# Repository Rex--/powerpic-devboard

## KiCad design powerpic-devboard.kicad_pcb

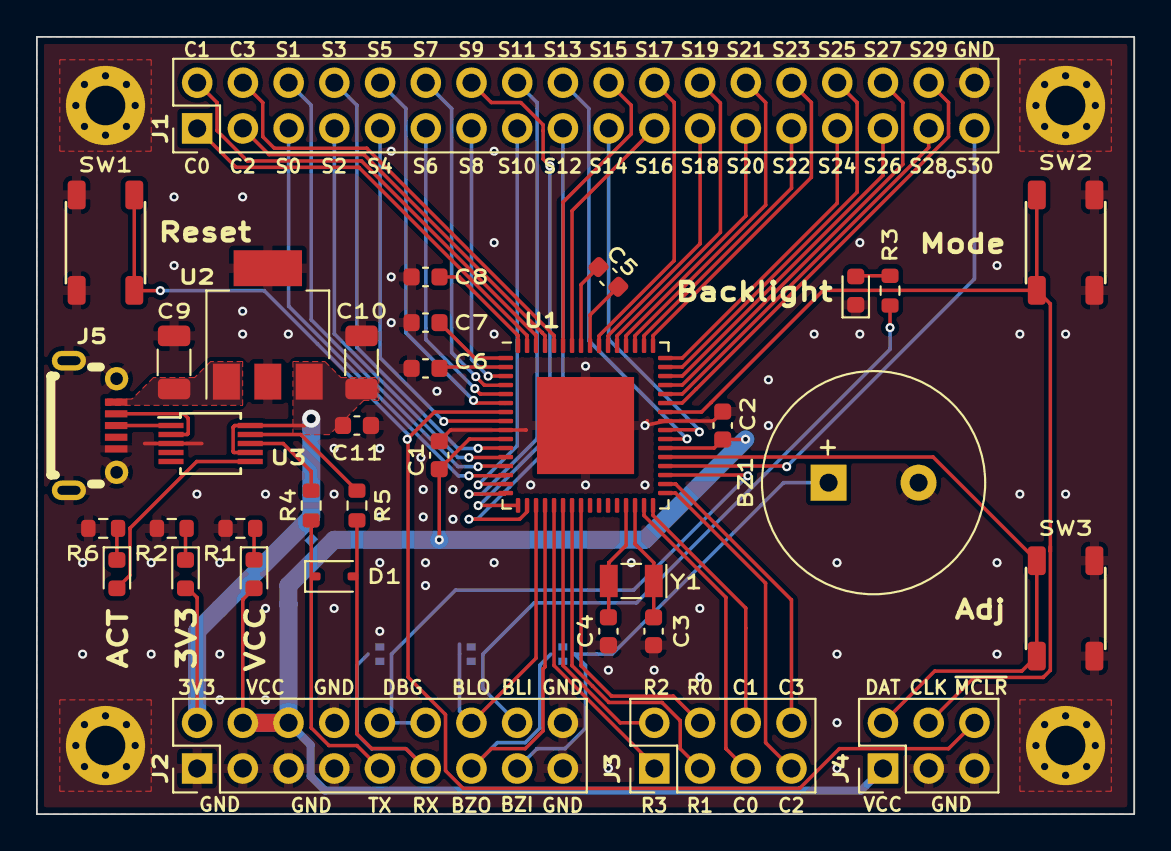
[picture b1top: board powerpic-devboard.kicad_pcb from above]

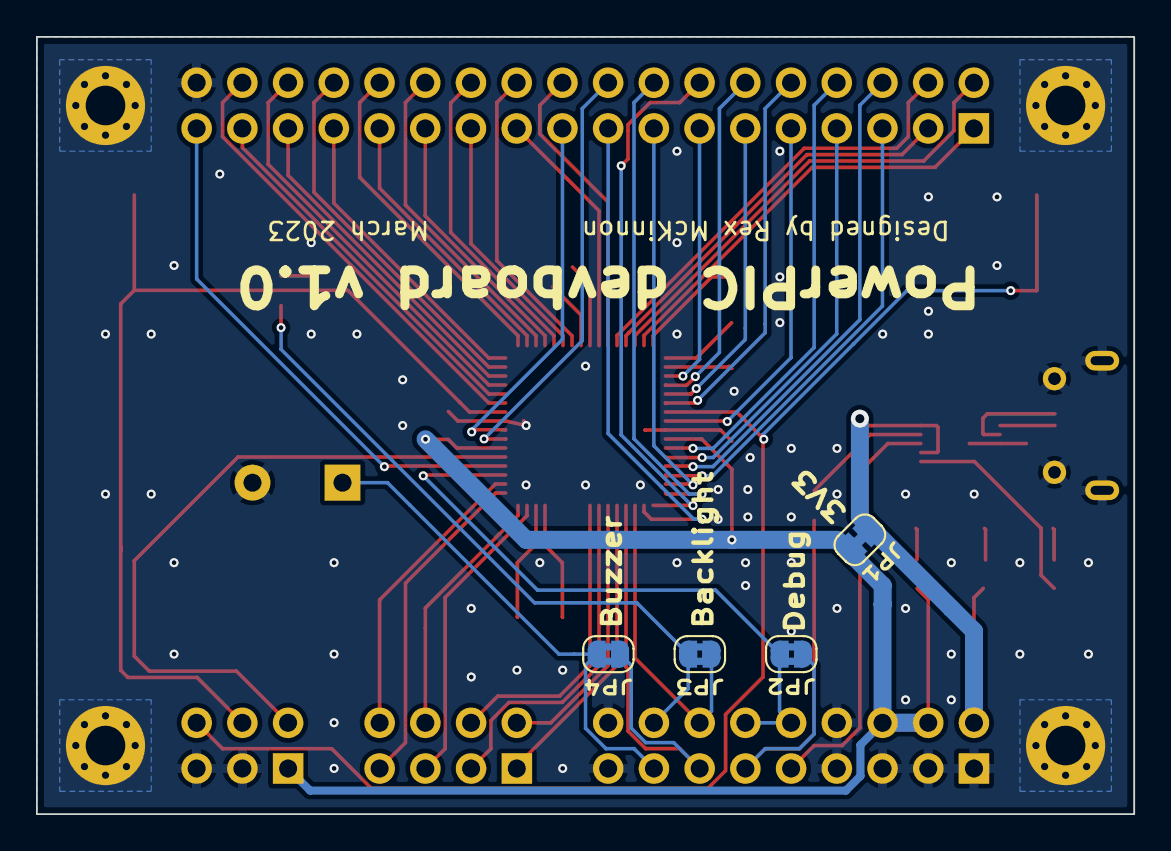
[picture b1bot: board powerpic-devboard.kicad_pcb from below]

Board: 2 copper layers, 61.0 x 43.2 mm, 43 parts (4 on the bottom side), 73 nets.

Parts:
BZ1: Buzzer; Buzzer_12.2x6.5RM5
C1, C2, C11: 0.1µF; C_0603_1608Metric
C3, C4: TBD; C_0603_1608Metric
C5: 1μF; C_0603_1608Metric
C6, C7, C8: 0.27μF; C_0603_1608Metric
C9, C10: 4.7µF; C_1206_3216Metric
D1: D; D_SOD-323
H1, H2, H3, H4: MountingHole_Pad; MountingHole_2.2mm_M2_Pad_Via
J1: Display; PinHeader_2x18_P2.54mm_Vertical
J2: Misc I/O; PinHeader_2x09_P2.54mm_Vertical
J3: Keypad; PinHeader_2x04_P2.54mm_Vertical
J4: ICSP; PinHeader_2x03_P2.54mm_Vertical
J5: Micro USB; USB_Micro-B_Receptacle_AdamTech_MCR-B-S-RA-SMT-CS5A-NF-TR
JP1: 3V3_en; SolderJumper-2_P1.3mm_Bridged_RoundedPad1.0x1.5mm
JP2: Debug_en; SolderJumper-2_P1.3mm_Bridged2Bar_RoundedPad1.0x1.5mm
JP3: Backlight_en; SolderJumper-2_P1.3mm_Bridged2Bar_RoundedPad1.0x1.5mm
JP4: Buzzer_en; SolderJumper-2_P1.3mm_Bridged2Bar_RoundedPad1.0x1.5mm
LED1: VCC; LED_0603_1608Metric
LED2: 3V3; LED_0603_1608Metric
LED3: Backlight; LED_0603_1608Metric
LED4: ACT; LED_0603_1608Metric
R1, R2, R4, R5, R6: R; R_0603_1608Metric
R3: TBD; R_0603_1608Metric
SW1: Reset; Button_Push_SPST_C&K_PTS647Sx38SMTR2LFS
SW2: Mode; Button_Push_SPST_C&K_PTS647Sx38SMTR2LFS
SW3: Adj; Button_Push_SPST_C&K_PTS647Sx38SMTR2LFS
U1: PIC16LF19197-xMR; QFN-64-1EP_9x9mm_P0.5mm_EP5.4x5.4mm
U2: AP2114; SOT-223-3_TabPin2
U3: CH340E; MSOP-10_3x3mm_P0.5mm
Y1: 32.768kHz; Crystal_SMD_MicroCrystal_CC7V-T1A-2Pin_3.2x1.5mm

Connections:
+3V3: C10.1, C11.2, J2.2, JP1.1 (A), LED2.2 (A), U2.3 (VO), U3.7 (VCC), U3.10 (V3)
/BACKLIGHT: J2.14, JP3.1 (A), U1.19 (COM7/SEG15/RG7)
/BACKLIGHT_LED: J2.16, JP3.2 (B), R3.1
/BUZZER: J2.13, JP4.1 (A), U1.20 (COM6/RG6)
/BUZZER_ONB: BZ1.1 (-), J2.15, JP4.2 (B)
/COL0: J3.5, U1.31 (RC6/SEG27)
/COL1: J3.6, U1.32 (RC7/SEG28)
/COL2: J3.7, U1.33 (RC2/SEG13)
/COL3: J3.8, U1.34 (RC3/SEG17)
/COM0: J1.1, U1.63 (COM0/RE3)
/COM1: J1.2, U1.62 (COM1/RE4)
/COM2: J1.3, U1.61 (COM2/RE5)
/COM3: J1.4, U1.60 (COM3/RE6)
/DEBUG: J2.10, J2.12, JP2.2 (B), U1.35 (RC4/SEG16)
/ICSP_CLK: J4.4, SW2.2, U1.42 (RB6/SEG38/ICSPCLK)
/ICSP_DAT: J4.2, SW3.1, U1.37 (RB7/SEG39/ICSPDAT)
/ROW0: J3.4, U1.24 (RA0/SEG33)
/ROW1: J3.3, U1.23 (RA1/SEG18)
/ROW2: J3.2, U1.22 (RA2/SEG34)
/ROW3: J3.1, U1.21 (RA3/SEG35)
/SEG0: J1.5, U1.14 (SEG22/RF4)
/SEG1: J1.6, U1.13 (SEG23/RF5)
/SEG2: J1.7, U1.12 (SEG24/RF6)
/SEG3: J1.8, U1.11 (SEG25/RF7)
/SEG4: J1.9, U1.8 (SEG26/RG4)
/SEG5: J1.10, U1.6 (SEG45/RG3)
/SEG6: J1.11, U1.5 (SEG44/RG2)
/SEG7: J1.12, U1.4 (SEG43/RG1)
/SEG8: J1.13, U1.3 (SEG42/RG0)
/SEG9: J1.14, U1.17 (SEG19/RF1)
/SEG10: J1.15, U1.15 (SEG21/RF3)
/SEG11: J1.16, U1.16 (SEG20/RF2)
/SEG12: J1.17, U1.18 (SEG41/RF0)
/SEG13: J1.18, U1.39 (RA7/SEG37)
/SEG14: J1.19, U1.40 (RA6/SEG36)
/SEG15: J1.20, U1.59 (SEG31/RE7)
/SEG16: J1.21, U1.58 (RD0/SEG0)
/SEG17: J1.22, U1.55 (RD1/SEG1)
/SEG18: J1.23, U1.54 (RD2/SEG2)
/SEG19: J1.24, U1.53 (RD3/SEG3)
/SEG20: J1.25, U1.52 (RD4/SEG4)
/SEG21: J1.26, U1.51 (RD5/SEG5)
/SEG22: J1.27, U1.50 (RD6/SEG6)
/SEG23: J1.28, U1.49 (RD7/SEG7)
/SEG24: J1.29, U1.48 (RB0/SEG30)
/SEG25: J1.30, U1.47 (RB1/SEG8)
/SEG26: J1.31, U1.46 (RB2/SEG9)
/SEG27: J1.32, U1.45 (RB3/SEG10)
/SEG28: J1.33, U1.44 (RB4/SEG11)
/SEG29: J1.34, U1.43 (RB5/SEG29)
/SEG30: J1.35, U1.36 (RC5/SEG12)
/UART_RX: D1.2 (A), J2.11, JP2.1 (A), R5.2
/UART_TX: D1.1 (K), J2.9, R4.2
/~MCLR: J4.6, SW1.2, U1.7 (VPP/~MCLR/RG5)
GND: BZ1.2 (+), C1.2, C2.2, C3.2, C4.2, C6.2, C7.2, C8.2, C9.2, C10.2, C11.1, H1.1, H2.1, H3.1, H4.1, J1.36, J2.1, J2.3, J2.5, J2.7, J2.8, J2.17, J2.18, J4.3, J4.5, J5.5 (GND), J5.6 (Shield), LED3.1 (K), R1.2, R2.2, R6.2, SW1.1, SW2.1, SW3.2, U1.9 (VSS), U1.41 (VSS), U1.65 (VSS), U2.2 (GND), U3.3 (GND)
unnamed: J5.3 (D+), U3.1 (UD+)
unnamed: J5.2 (D-), U3.2 (UD-)
unnamed: LED1.1 (K), R1.1
unnamed: LED2.1 (K), R2.1
unnamed: LED3.2 (A), R3.2
unnamed: LED4.2 (A), U3.6 (TNOW)
unnamed: LED4.1 (K), R6.1
unnamed: C5.2, U1.57 (CFLY1/SEG32/RH2)
unnamed: C5.1, U1.56 (CFLY2/SEG40/RH3)
unnamed: C3.1, U1.30 (RC0), Y1.1
unnamed: C4.1, U1.29 (RC1), Y1.2
unnamed: C6.1, U1.2 (VLCD1/RE0)
unnamed: C7.1, U1.1 (VLCD2/RE1)
unnamed: C8.1, U1.64 (VLCD3)
unnamed: R5.1, U3.9 (RXD)
unnamed: R4.1, U3.8 (TXD)
VBUS: C9.1, J5.1 (VBUS), U2.1 (VI)
VCC: C1.1, C2.1, J2.4, J2.6, J4.1, JP1.2 (B), LED1.2 (A), U1.10 (VDD), U1.38 (VDD)

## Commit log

2023-03-09 Sent v1.0 to fab
